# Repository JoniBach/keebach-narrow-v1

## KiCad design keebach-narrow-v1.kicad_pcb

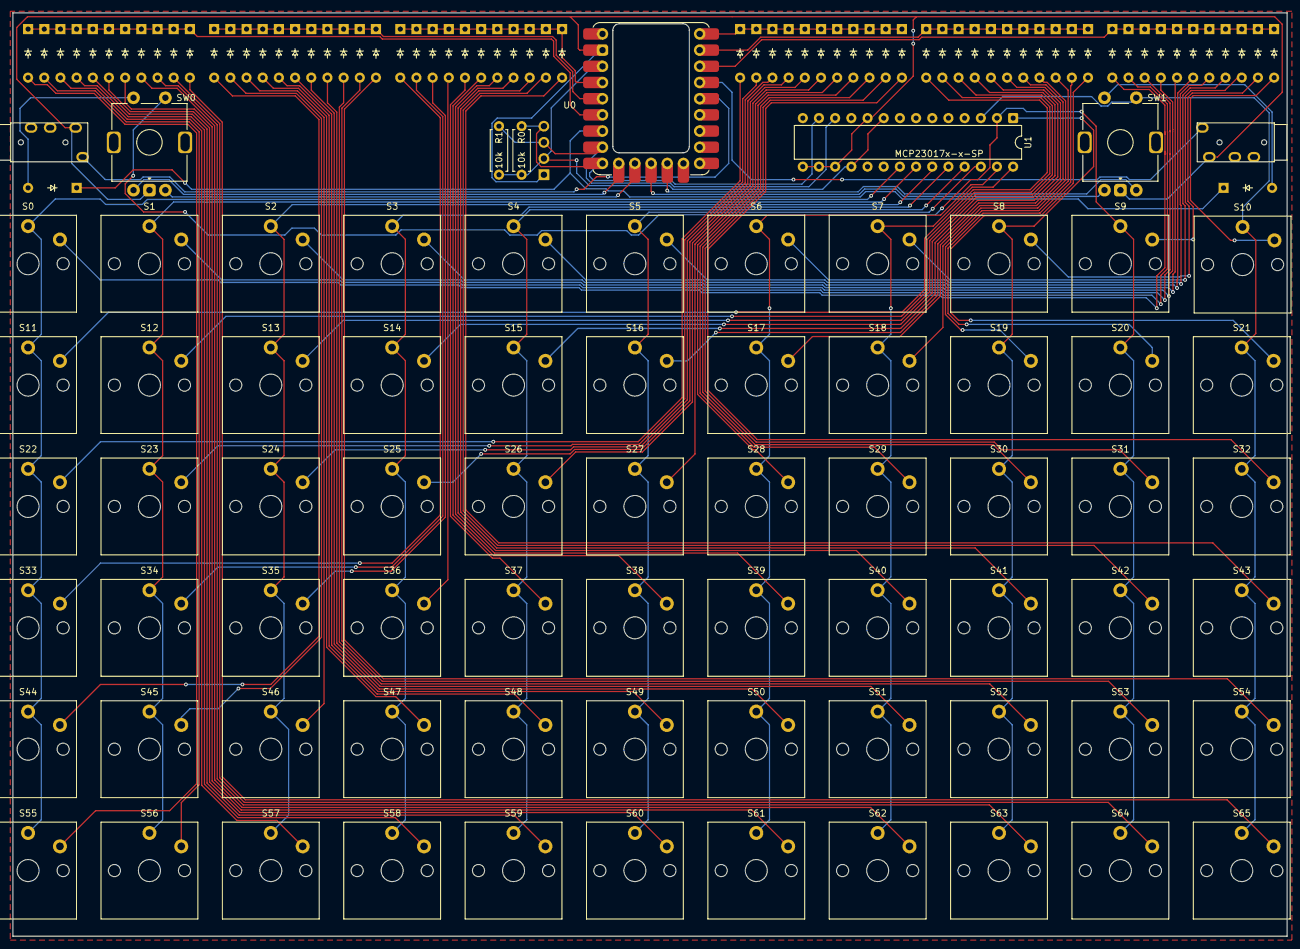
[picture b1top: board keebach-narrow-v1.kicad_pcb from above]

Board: 2 copper layers, 200.0 x 144.9 mm, 143 parts (0 on the bottom side), 96 nets.

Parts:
D0, D1, D2, D3, D4, D5, D6, D7, D8, D9, D10, D11, D12, D13, D14, D15, D16, D17, D18, D19, D20, D21, D22, D23, D24, D25, D26, D27, D28, D29, D30, D31, D32, D33, D34, D35, D36, D37, D38, D39, D40, D41, D42, D43, D44, D45, D46, D47, D48, D49, D50, D51, D52, D53, D54, D55, D56, D57, D58, D59, D60, D61, D62, D63, D64, D65, D66, D67: Diode_DO-35
J1: OLED_128x32
R0, R1: 10k; R_Axial_DIN0207_L6.3mm_D2.5mm_P7.62mm_Horizontal
S0, S1, S2, S3, S4, S5, S6, S7, S8, S9, S10, S11, S12, S13, S14, S15, S16, S17, S18, S19, S20, S21, S22, S23, S24, S25, S26, S27, S28, S29, S30, S31, S32, S33, S34, S35, S36, S37, S38, S39, S40, S41, S42, S43, S44, S45, S46, S47, S48, S49, S50, S51, S52, S53, S54, S55, S56, S57, S58, S59, S60, S61, S62, S63, S64, S65: Choc_V1_1.00u
SW0, SW1: RotaryEncoder_Switch; ROT_Alps_EC11E-Switch
U0: RP2040-Matrix; RP2040-Matrix_ACH
U1: MCP23017x-x-SP; DIP-28_W7.62mm
U2, U3: TRRS; TRRS_PJ-320A

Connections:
3V3: J1.2 (VCC), R0.2, R1.2, U0.3 (3V3), U1.9 (V_{DD}), U1.18 (~RESET)
COL_0: S0.1, S11.1, S22.1, S33.1, S44.1, S55.1, U1.21 (GPA0)
COL_1: S1.1, S12.1, S23.1, S34.1, S45.1, S56.1, U1.22 (GPA1)
COL_2: S2.1, S13.1, S24.1, S35.1, S46.1, S57.1, U1.23 (GPA2)
COL_3: S3.1, S14.1, S25.1, S36.1, S47.1, S58.1, U1.24 (GPA3)
COL_4: S4.1, S15.1, S26.1, S37.1, S48.1, S59.1, U1.25 (GPA4)
COL_5: S5.1, S16.1, S27.1, S38.1, S49.1, S60.1, U1.26 (GPA5)
COL_6: S6.1, S17.1, S28.1, S39.1, S50.1, S61.1, U1.27 (GPA6)
COL_7: S7.1, S18.1, S29.1, S40.1, S51.1, S62.1, U1.28 (GPA7)
COL_8: S8.1, S19.1, S30.1, S41.1, S52.1, S63.1, U1.1 (GPB0)
COL_9: S9.1, S20.1, S31.1, S42.1, S53.1, S64.1, SW0.S1, U1.2 (GPB1)
COL_10: S10.1, S21.1, S32.1, S43.1, S54.1, S65.1, SW1.S1, U1.3 (GPB2)
GND: J1.1 (GND), SW0.C, SW1.C, U0.2 (GND), U1.10 (V_{SS}), U1.15 (A0), U1.16 (A1), U1.17 (A2), U2.2 (TIP), U3.2 (TIP)
unnamed: D0.2 (A), S0.2
unnamed: D1.2 (A), S1.2
unnamed: D2.2 (A), S2.2
unnamed: D3.2 (A), S3.2
unnamed: D4.2 (A), S4.2
unnamed: D5.2 (A), S5.2
unnamed: D6.2 (A), S6.2
unnamed: D7.2 (A), S7.2
unnamed: D8.2 (A), S8.2
unnamed: D9.2 (A), S9.2
unnamed: D10.2 (A), S10.2
unnamed: D11.2 (A), S11.2
unnamed: D12.2 (A), S12.2
unnamed: D13.2 (A), S13.2
unnamed: D14.2 (A), S14.2
unnamed: D15.2 (A), S15.2
unnamed: D16.2 (A), S16.2
unnamed: D17.2 (A), S17.2
unnamed: D18.2 (A), S18.2
unnamed: D19.2 (A), S19.2
unnamed: D20.2 (A), S20.2
unnamed: D21.2 (A), S21.2
unnamed: D22.2 (A), S22.2
unnamed: D23.2 (A), S23.2
unnamed: D24.2 (A), S24.2
unnamed: D25.2 (A), S25.2
unnamed: D26.2 (A), S26.2
unnamed: D27.2 (A), S27.2
unnamed: D28.2 (A), S28.2
unnamed: D29.2 (A), S29.2
unnamed: D30.2 (A), S30.2
unnamed: D31.2 (A), S31.2
unnamed: D32.2 (A), S32.2
unnamed: D33.2 (A), S33.2
unnamed: D34.2 (A), S34.2
unnamed: D35.2 (A), S35.2
unnamed: D36.2 (A), S36.2
unnamed: D37.2 (A), S37.2
unnamed: D38.2 (A), S38.2
unnamed: D39.2 (A), S39.2
unnamed: D40.2 (A), S40.2
unnamed: D41.2 (A), S41.2
unnamed: D42.2 (A), S42.2
unnamed: D43.2 (A), S43.2
unnamed: D44.2 (A), S44.2
unnamed: D45.2 (A), S45.2
unnamed: D46.2 (A), S46.2
unnamed: D47.2 (A), S47.2
unnamed: D48.2 (A), S48.2
unnamed: D49.2 (A), S49.2
unnamed: D50.2 (A), S50.2
unnamed: D51.2 (A), S51.2
unnamed: D52.2 (A), S52.2
unnamed: D53.2 (A), S53.2
unnamed: D54.2 (A), S54.2
unnamed: D55.2 (A), S55.2
unnamed: D56.2 (A), S56.2
unnamed: D57.2 (A), S57.2
unnamed: D58.2 (A), S58.2
unnamed: D59.2 (A), S59.2
unnamed: D60.2 (A), S60.2
unnamed: D61.2 (A), S61.2
unnamed: D62.2 (A), S62.2
unnamed: D63.2 (A), S63.2
unnamed: D64.2 (A), S64.2
unnamed: D65.2 (A), S65.2
unnamed: D66.2 (A), SW0.S2
unnamed: D67.2 (A), SW1.S2
ROW_0: D66.1 (K), D67.1 (K), U0.7 (P26)
ROW_1: D0.1 (K), D1.1 (K), D2.1 (K), D3.1 (K), D4.1 (K), D5.1 (K), D6.1 (K), D7.1 (K), D8.1 (K), D9.1 (K), D10.1 (K), U0.12 (P2)
ROW_2: D11.1 (K), D12.1 (K), D13.1 (K), D14.1 (K), D15.1 (K), D16.1 (K), D17.1 (K), D18.1 (K), D19.1 (K), D20.1 (K), D21.1 (K), U0.11 (P1)
ROW_3: D22.1 (K), D23.1 (K), D24.1 (K), D25.1 (K), D26.1 (K), D27.1 (K), D28.1 (K), D29.1 (K), D30.1 (K), D31.1 (K), D32.1 (K), U0.10 (P0)
ROW_4: D33.1 (K), D34.1 (K), D35.1 (K), D36.1 (K), D37.1 (K), D38.1 (K), D39.1 (K), D40.1 (K), D41.1 (K), D42.1 (K), D43.1 (K), U0.4 (P29)
ROW_5: D44.1 (K), D45.1 (K), D46.1 (K), D47.1 (K), D48.1 (K), D49.1 (K), D50.1 (K), D51.1 (K), D52.1 (K), D53.1 (K), D54.1 (K), U0.5 (P28)
ROW_6: D55.1 (K), D56.1 (K), D57.1 (K), D58.1 (K), D59.1 (K), D60.1 (K), D61.1 (K), D62.1 (K), D63.1 (K), D64.1 (K), D65.1 (K), U0.6 (P27)
SCL: J1.3 (SCL), R1.1, U0.8 (P15), U1.12 (SCK)
SDA: J1.4 (SDA), R0.1, U0.9 (P14), U1.13 (SDA)
SW0_A: SW0.A, U0.19 (P13)
SW0_B: SW0.B, U0.20 (P12)
SW1_A: SW1.A, U0.21 (P11)
SW1_B: SW1.B, U0.22 (P10)
U0_TRRS: U0.13 (P3), U2.1 (SLEEVE)
U1_TRRS: U0.14 (P4), U3.1 (SLEEVE)
